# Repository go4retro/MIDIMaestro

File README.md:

# TANDY Color Computer 1/2/3/Dragon MIDI Interface

V1 is a direct transcription of the original Rulaford MIDI interface design (that itself seems to be essentially a reference design used by almost all Motorola-bus systems of the day)

V2 switches out the 74ls90 for a 74ls161 counter (easier to source), but leaves the crystal design.  It also adds in some optional blinkenlights

V3 switches to a crystal oscillator and repurposes some of the now unused gates.

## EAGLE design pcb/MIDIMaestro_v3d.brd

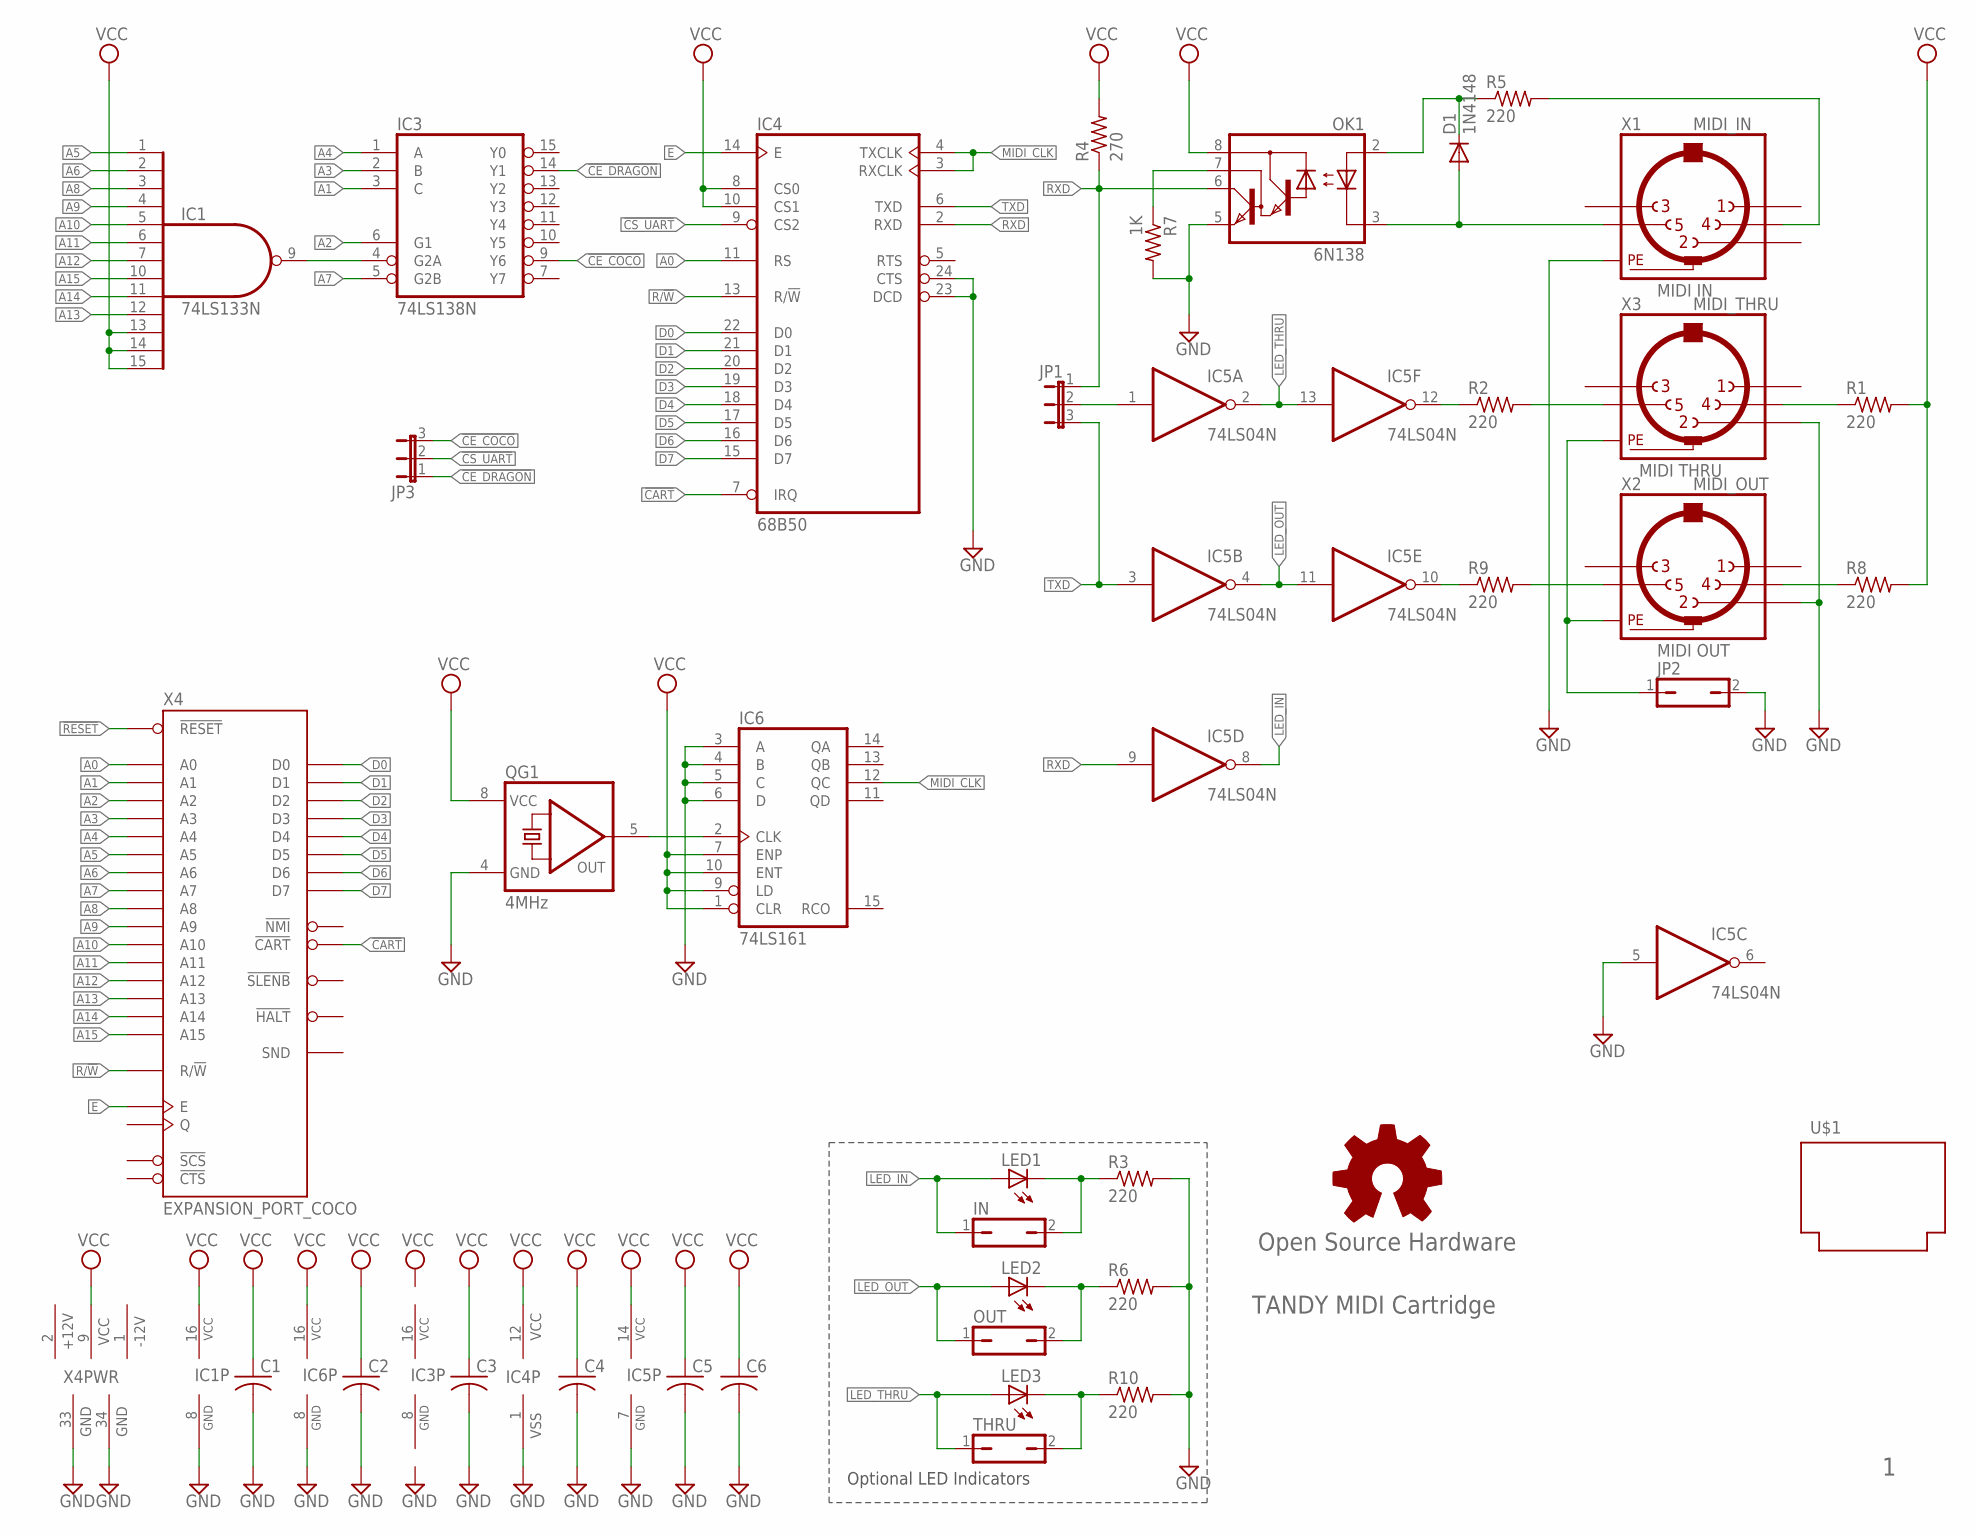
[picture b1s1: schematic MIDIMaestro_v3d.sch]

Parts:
C1, C2, C3, C4, C5, C6: C-US025-025X050; C025-025X050
D1: 1N4148; DO35-7
GOLD_ORB_SM1: Open Source Hardware; OSHW_8MM
IC1: 74LS133N; DIL16-RP
IC3: 74LS138N; DIL16-RP
IC4: 68B50; DIL24-ROUNDPAD
IC5: 74LS04N; DIL14-RP
IC6: 74LS161; DIL16-RP
IN: JP1Q; JP1
JP1, JP3: JP2E; JP2
JP2: JP1Q; JP1
LED1, LED2, LED3: LED3MM
OK1: 6N138; DIL08
OUT: JP1Q; JP1
QG1: 4MHz; DIL08S
R1, R2, R3, R5, R6, R8, R9, R10: 220; 0204/7
R4: 270; 0204/7
R7: 1K; 0204/7
THRU: JP1Q; JP1
U$1: PROGRAM_PAK
X1: MIDI_IN; MAB5SH
X2: MIDI_OUT; MAB5SH
X3: MIDI_THRU; MAB5SH
X4: EXPANSION_PORT_COCO; MA20-2

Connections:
!CART: IC4.7 (IRQ), X4.8 (!CART)
!CE_COCO: IC3.9 (Y6), JP3.3
!CE_DRAGON: IC3.14 (Y1), JP3.1
!CS_UART: IC4.9 (CS2), JP3.2
!RESET: X4.5 (!RESET)
+12V: X4.2 (+12V)
-12V: X4.1 (-12V)
A0: IC4.11 (RS), X4.19 (A0)
A1: IC3.3 (C), X4.20 (A1)
A2: IC3.6 (G1), X4.21 (A2)
A3: IC3.2 (B), X4.22 (A3)
A4: IC3.1 (A), X4.23 (A4)
A5: IC1.1 (I0), X4.24 (A5)
A6: IC1.2 (I1), X4.25 (A6)
A7: IC3.5 (G2B), X4.26 (A7)
A8: IC1.3 (I2), X4.27 (A8)
A9: IC1.4 (I3), X4.28 (A9)
A10: IC1.5 (I4), X4.29 (A10)
A11: IC1.6 (I5), X4.30 (A11)
A12: IC1.7 (I6), X4.31 (A12)
A13: IC1.12 (I9), X4.37 (A13)
A14: IC1.11 (I8), X4.38 (A14)
A15: IC1.10 (I7), X4.39 (A15)
D0: IC4.22 (D0), X4.10 (D0)
D1: IC4.21 (D1), X4.11 (D1)
D2: IC4.20 (D2), X4.12 (D2)
D3: IC4.19 (D3), X4.13 (D3)
D4: IC4.18 (D4), X4.14 (D4)
D5: IC4.17 (D5), X4.15 (D5)
D6: IC4.16 (D6), X4.16 (D6)
D7: IC4.15 (D7), X4.17 (D7)
E: IC4.14 (E), X4.6 (E)
GND: C1.2, C2.2, C3.2, C4.2, C5.2, C6.2, IC1.8 (GND), IC3.8 (GND), IC4.1 (VSS), IC4.23 (DCD), IC4.24 (CTS), IC5.5 (I), IC5.7 (GND), IC6.3 (A), IC6.4 (B), IC6.5 (C), IC6.6 (D), IC6.8 (GND), JP2.2, OK1.5 (GND), QG1.4 (GND), R3.2, R6.2, R7.2, R10.2, X1.PE, X1.PE@ (PE), X2.2, X3.2, X4.33 (GND), X4.34 (GND)
LED_IN: IC5.8 (O), IN.1, LED1.A
LED_OUT: IC5.4 (O), IC5.11 (I), LED2.A, OUT.1
LED_THRU: IC5.2 (O), IC5.13 (I), LED3.A, THRU.1
MIDI_CLK: IC4.3 (RXCLK), IC4.4 (TXCLK), IC6.12 (QC)
unnamed: R9.2, X2.5
unnamed: JP2.1, X2.PE, X2.PE@ (PE), X3.PE, X3.PE@ (PE)
unnamed: R8.1, X2.4
unnamed: IC5.10 (O), R9.1
unnamed: D1.C, OK1.2 (A), R5.1
unnamed: R5.2, X1.4
unnamed: D1.A, OK1.3 (C), X1.5
unnamed: OK1.7 (VB), R7.1
unnamed: R2.2, X3.5
unnamed: IC5.12 (O), R2.1
unnamed: IN.2, LED1.K (C), R3.1
unnamed: R1.1, X3.4
unnamed: IC1.9 (O), IC3.4 (G2A)
unnamed: IC6.2 (CLK), QG1.5 (OUT)
unnamed: IC5.1 (I), JP1.2
unnamed: LED2.K (C), OUT.2, R6.1
unnamed: LED3.K (C), R10.1, THRU.2
R/!W: IC4.13 (R/!W), X4.18 (R/!W)
RXD: IC4.2 (RXD), IC5.9 (I), JP1.1, OK1.6 (VO), R4.1
TXD: IC4.6 (TXD), IC5.3 (I), JP1.3
VCC: C1.1, C2.1, C3.1, C4.1, C5.1, C6.1, IC1.13 (I10), IC1.14 (I11), IC1.15 (I12), IC1.16 (VCC), IC3.16 (VCC), IC4.8 (CS0), IC4.10 (CS1), IC4.12 (VCC), IC5.14 (VCC), IC6.1 (CLR), IC6.7 (ENP), IC6.9 (LD), IC6.10 (ENT), IC6.16 (VCC), OK1.8 (VCC), QG1.8 (VCC), R1.2, R4.2, R8.2, X4.9 (VCC)

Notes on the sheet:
TANDY MIDI Cartridge
MIDI OUT
MIDI IN
MIDI THRU
Optional LED Indicators

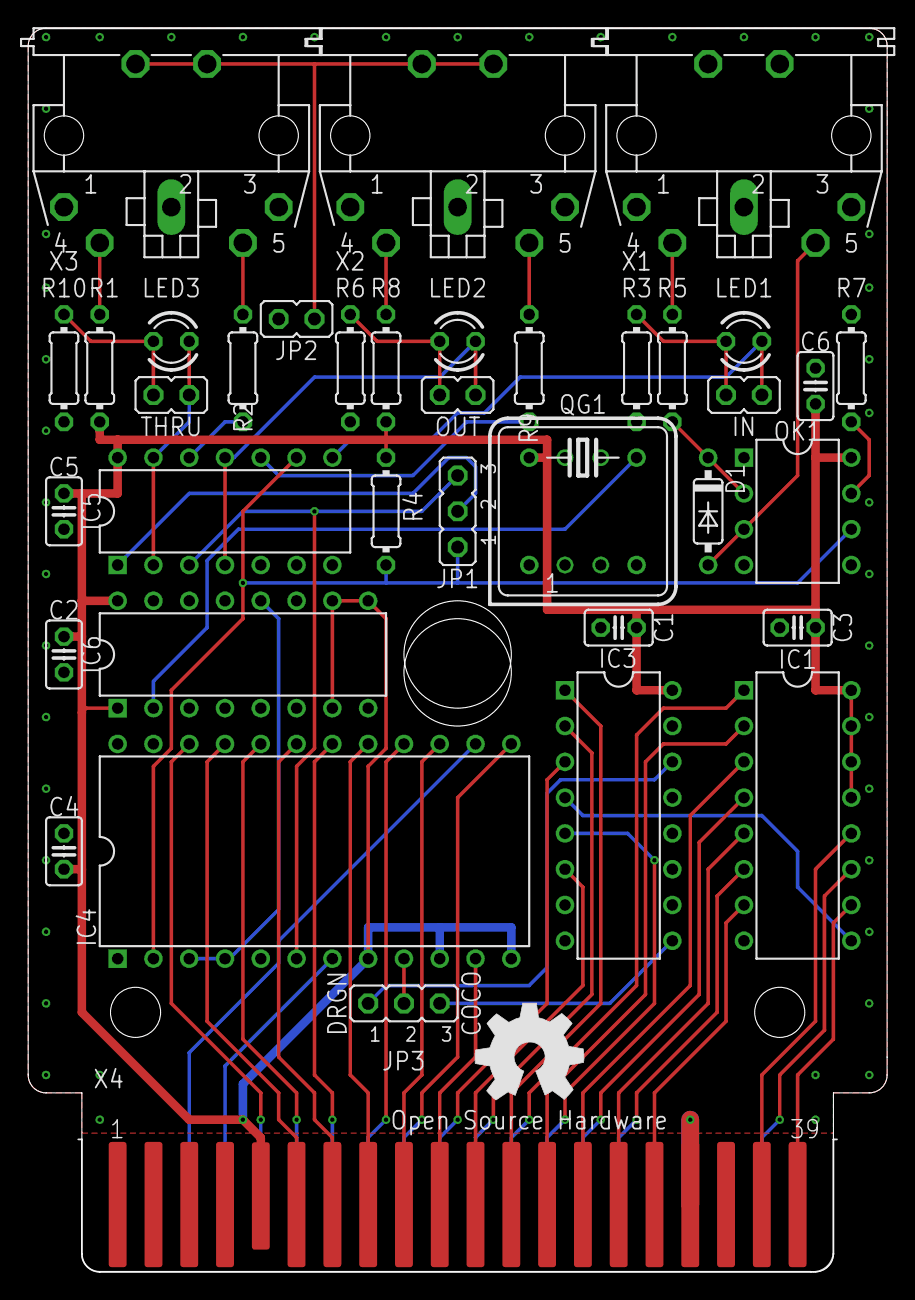
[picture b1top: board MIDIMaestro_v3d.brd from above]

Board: 2 copper layers, 61.0 x 88.3 mm, 39 parts (0 on the bottom side), 55 nets.

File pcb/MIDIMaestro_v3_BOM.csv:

Parts,Qty,Value,Device,Description,Part number
"C1, C2, C3, C4, C5, C6",6,,C-US025-025X050,"CAPACITOR, American symbol",BC3324-ND 
JP1,1,,JP2E,JUMPER,EDJ1G0
JP2,1,,JP1Q,JUMPER,EDJ1G0
JP3,1,,JP1Q,JUMPER,EDJ1G0
LED1,1,,LED3MM,LED,1080-1113-ND 
LED2,1,,LED3MM,LED,1125-1182-ND 
LED3,1,,LED3MM,LED,754-1220-ND 
R7,1,1K,R-US_0204/7,"RESISTOR, American symbol",CF14JT1K00
D1,1,1N4148DO35-7,1N4148DO35-7,DIODE,1N4148-TPMSCT-ND 
"R1, R2, R3, R5, R6, R8, R9, R10",8,220R,R-US_0204/7,"RESISTOR, American symbol",CF14JT220R
R4,1,270R,R-US_0204/7,"RESISTOR, American symbol",CF14JT270R
QG1,1,4MHz,QG5460,CRYSTAL RESONATOR,SG-531P 4.0000MC: ROHS
IC4,1,68B50,6850-RP,MICROCONTROLLER/MEMORY DEVICE,MC68B50
OK1,1,6N138,6N138,MOTOROLA OPTO COUPLER,160-1795-ND 
IC6,1,74*161,74160N,Synchronous 4-bit COUNTER,296-8244-5-ND 
IC5,1,74LS04N,74LS04N,Hex INVERTER,SN74HCT04N
IC1,1,74LS133N,74S133N,13-input NAND gate,74LS133
IC3,1,74LS138N,74LS138N,3-line to 8-line DECODER/DEMULTIPLEXER,SN74AHCT138N
"X1,X2,X3",3,MIDI,MAB5SH,Female CONNECTOR,SDS-50J
,1,8 pin socket,,,2057-ICS-308-T-ND 
,1,14 pin socket,,,2057-ICS-314-T-ND 
,3,16 pin socket,,,2057-ICS-316-T-ND 
,1,"24 pin socket .6""",,,2057-ICS-624-T-ND 
,,,,,
,,,,,
,,,,,
,,,,,
,,,,,
,,,,,
,,,,,
,,,,,
,,,,,
,,,,,
,,,,,
,,,,,
,,,,,
,,,,,
,,,,,
,,,,,

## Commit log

2020-01-09 Fixed polarity issues with LED signals
2020-01-11 Cart port connector was slightly narrow. Widened.
2020-03-08 Changed name, Added Dragon variant
2020-03-08 Add PNG opf V3 Dragon Schematic
2020-04-15 Added other BOM formats
2020-04-15 Cleaned up alternate BOM formats
